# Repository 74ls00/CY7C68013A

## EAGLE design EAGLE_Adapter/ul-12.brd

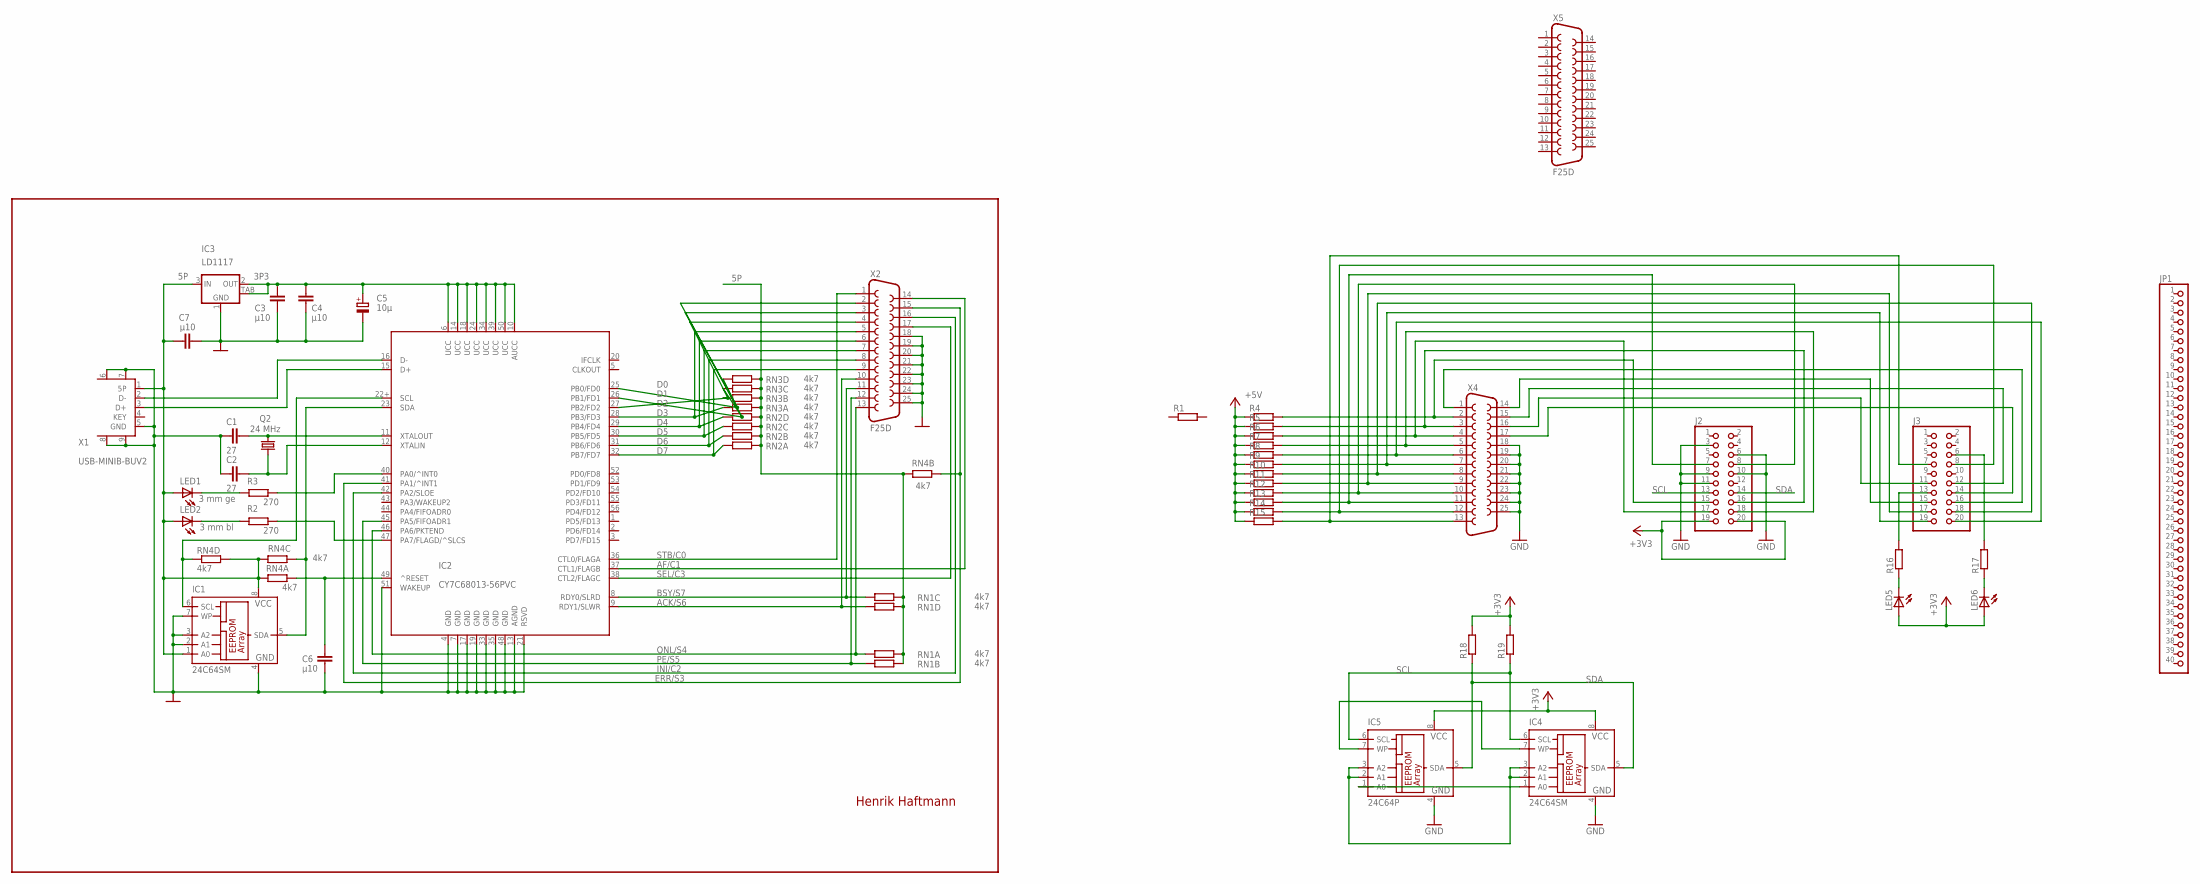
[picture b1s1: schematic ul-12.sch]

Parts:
C1, C2: 27; C0805
C3, C4, C6, C7: µ10; C0805
C5: 10µ; C/6032-28R
IC1, IC4: 24C64SM; SO-08M
IC2: CY7C68013-56PVC; SSOP56
IC3: LD1117; SOT223
IC5: 24C64P; DIL8
J2, J3: PINHD-2X10; 2X10
JP1: PINHD-1X40; 1X40
LED1: 3 mm ge; LED3MM
LED2: 3 mm bl; LED3MM
LED5, LED6: LEDSML0805; SML0805
Q2: 24 MHz; HC49U-V
R1, R4, R5, R6, R7, R8, R9, R10, R11, R12, R13, R14, R15, R18, R19: R-EU_R0805; R0805
R2, R3: 270; R0805
R16, R17: R-EU_0207/12; 0207/12
RN1, RN2, RN3, RN4: 4k7; R-4P
X1: USB-MINIB-BUV2; USB-MINIB-BUO
X2, X5: F25D
X4: F25HP

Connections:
3P3: C3.2, C4.2, C5.+, IC2.6 (UCC), IC2.10 (AUCC), IC2.14 (UCC), IC2.18 (UCC), IC2.24 (UCC), IC2.34 (UCC), IC2.39 (UCC), IC2.50 (UCC), IC3.2 (OUT), IC3.TAB (OUT)
5P: C7.2, IC1.1 (A0), IC1.8 (VCC), IC3.3 (IN), LED1.A, LED2.A, RN1.5 (2), RN1.6 (2), RN1.7 (2), RN1.8 (2), RN2.5 (2), RN2.6 (2), RN2.7 (2), RN2.8 (2), RN3.5 (2), RN3.6 (2), RN3.7 (2), RN3.8 (2), RN4.5 (2), RN4.6 (2), RN4.7 (2), RN4.8 (2), X1.1 (5P)
+3V3: IC4.8 (VCC), IC5.8 (VCC), J2.19, J2.20, LED5.A, LED6.A, R18.2, R19.2
+5V: R4.1, R5.1, R6.1, R7.1, R8.1, R9.1, R10.1, R11.1, R12.1, R13.1, R14.1, R15.1
ACK/S6: IC2.9 (RDY1/SLWR), RN1.4 (1), X2.10
AF/C1: IC2.37 (CTL1/FLAGB), X2.14
BSY/S7: IC2.8 (RDY0/SLRD), RN1.3 (1), X2.11
D0: IC2.25 (PB0/FD0), RN3.4 (1), X2.2
D1: IC2.26 (PB1/FD1), RN3.3 (1), X2.3
D2: IC2.27 (PB2/FD2), RN3.2 (1), X2.4
D3: IC2.28 (PB3/FD3), RN3.1, X2.5
D4: IC2.29 (PB4/FD4), RN2.4 (1), X2.6
D5: IC2.30 (PB5/FD5), RN2.3 (1), X2.7
D6: IC2.31 (PB6/FD6), RN2.2 (1), X2.8
D7: IC2.32 (PB7/FD7), RN2.1, X2.9
ERR/S3: IC2.41 (PA1/^INT1), RN4.2 (1), X2.15
GND: C1.2, C2.2, C3.1, C4.1, C5.-, C6.1, C7.1, IC1.2 (A1), IC1.3 (A2), IC1.4 (GND), IC1.7 (WP), IC2.4 (GND), IC2.7 (GND), IC2.13 (AGND), IC2.17 (GND), IC2.19 (GND), IC2.21 (RSVD), IC2.33 (GND), IC2.35 (GND), IC2.48 (GND), IC2.51 (WAKEUP), IC3.1 (GND), IC4.4 (GND), IC5.4 (GND), J2.3, J2.6, J2.9, J2.10, J2.11, X1.5 (GND), X1.6 (GND), X1.7 (GND), X1.8 (GND), X1.9 (GND), X2.18, X2.19, X2.20, X2.21, X2.22, X2.23, X2.24, X2.25, X4.18, X4.19, X4.20, X4.21, X4.22, X4.23, X4.24, X4.25
INI/C2: IC2.42 (PA2/SLOE), X2.16
unnamed: C2.1, IC2.12 (XTALIN), Q2.1
unnamed: C1.1, IC2.11 (XTALOUT), Q2.2
unnamed: IC2.16 (D-), X1.2 (D-)
unnamed: C6.2, IC2.49 (^RESET), RN4.1
unnamed: LED2.K (C), R2.1
unnamed: J3.16, X4.1
unnamed: LED1.K (C), R3.1
unnamed: IC2.47 (PA7/FLAGD/^SLCS), R2.2
unnamed: IC2.40 (PA0/^INT0), R3.2
unnamed: IC1.5 (SDA), IC2.23 (SDA), RN4.3 (1)
unnamed: IC1.6 (SCL), IC2.22+ (SCL), RN4.4 (1)
unnamed: J2.15, R4.2, X4.2
unnamed: J2.16, R5.2, X4.3
unnamed: J2.17, R6.2, X4.4
unnamed: J2.18, R7.2, X4.5
unnamed: J3.20, R8.2, X4.6
unnamed: J3.19, R9.2, X4.7
unnamed: J3.18, R10.2, X4.8
unnamed: J3.17, R11.2, X4.9
unnamed: J2.8, R12.2, X4.10
unnamed: J2.7, R13.2, X4.11
unnamed: J3.8, R14.2, X4.12
unnamed: J3.7, R15.2, X4.13
unnamed: IC4.7 (WP), IC5.7 (WP)
unnamed: J3.13, R16.2
unnamed: LED5.C, R16.1
unnamed: J3.6, R17.2
unnamed: LED6.C, R17.1
unnamed: IC2.15 (D+), X1.3 (D+)
unnamed: J3.14, X4.17
unnamed: J3.11, X4.16
unnamed: J3.12, X4.15
unnamed: J3.15, X4.14
unnamed: IC4.1 (A0), IC5.1 (A0)
unnamed: IC4.2 (A1), IC4.3 (A2), IC5.2 (A1), IC5.3 (A2)
ONL/S4: IC2.46 (PA6/PKTEND), RN1.1, X2.13
PE/S5: IC2.45 (PA5/FIFOADR1), RN1.2 (1), X2.12
SCL: IC4.6 (SCL), IC5.6 (SCL), J2.13, R19.1
SDA: IC4.5 (SDA), IC5.5 (SDA), J2.14, R18.1
SEL/C3: IC2.38 (CTL2/FLAGC), X2.17
STB/C0: IC2.36 (CTL0/FLAGA), X2.1

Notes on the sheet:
Henrik Haftmann

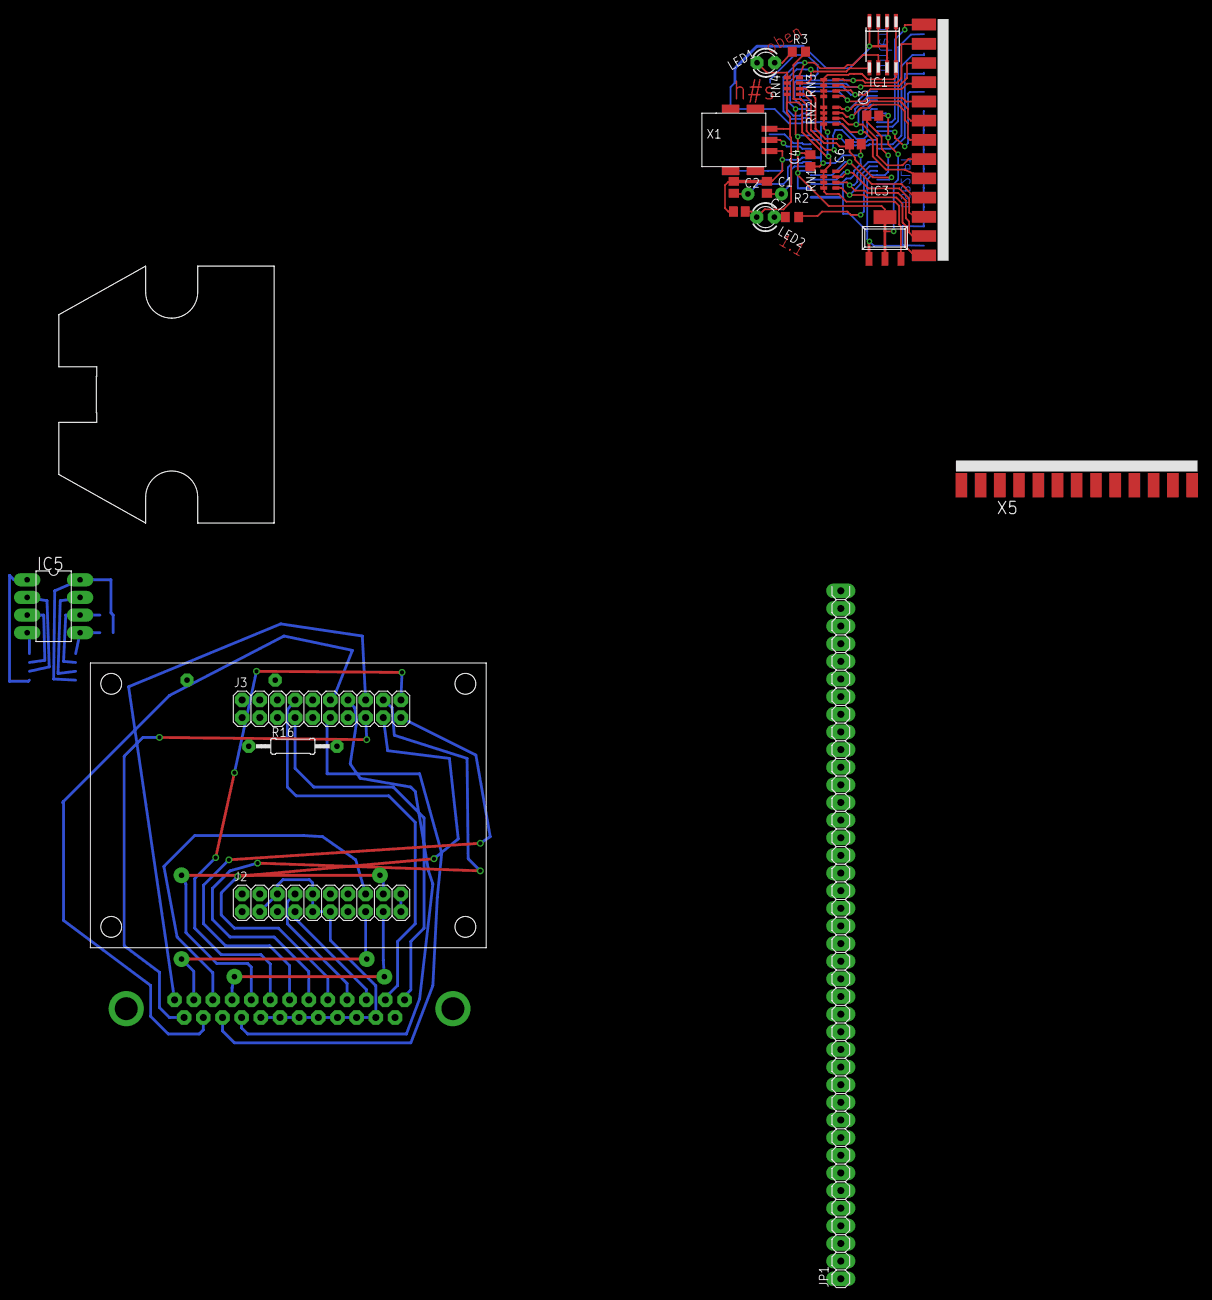
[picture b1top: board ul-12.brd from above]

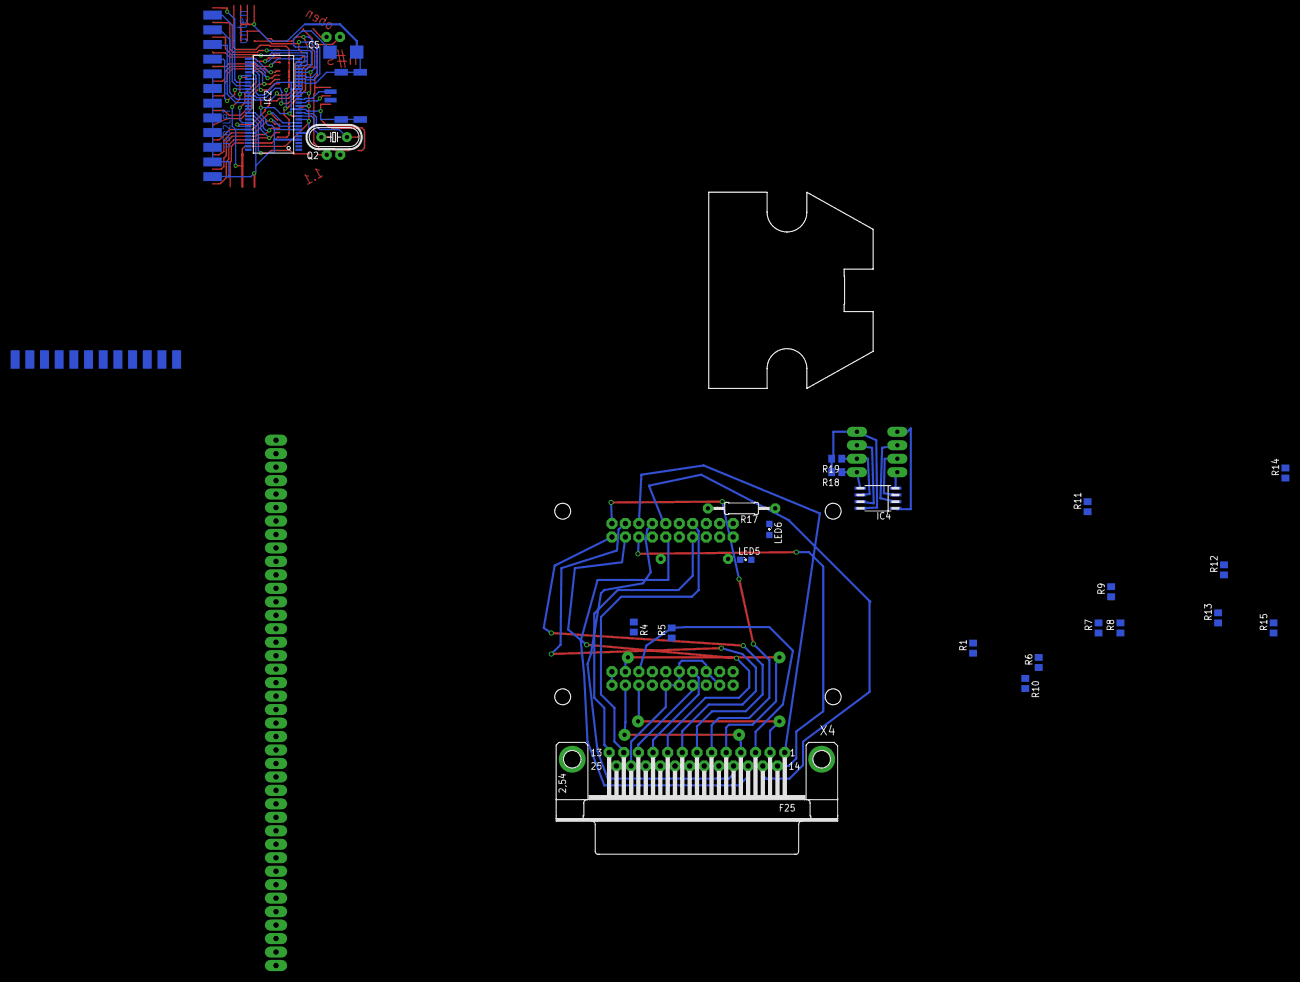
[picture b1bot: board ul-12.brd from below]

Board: 2 copper layers, 48 parts (23 on the bottom side), 59 nets.

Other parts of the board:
U$1: MINI
